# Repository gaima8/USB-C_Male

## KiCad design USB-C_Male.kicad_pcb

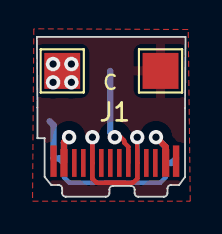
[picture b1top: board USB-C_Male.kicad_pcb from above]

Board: 2 copper layers, 8.3 x 8.9 mm, 4 parts (1 on the bottom side), 3 nets.

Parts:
J1: USB_C_Receptacle_PowerOnly_6P; USB_C_Plug_JAE_DX07P024AJ1
J2: V; TestPoint_Pad_2.0x2.0mm
J3: C; TestPoint_Pad_2.0x2.0mm
J4: G; TestPoint_Pad_2.0x2.0mm

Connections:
CC: J1.A5 (CC), J3.1
GND: J1.A1 (GND), J1.A12 (GND), J1.B1 (GND), J1.B12 (GND), J1.S1 (SHIELD), J4.1
VBUS: J1.A4 (VBUS), J1.A9 (VBUS), J1.B4 (VBUS), J1.B9 (VBUS), J2.1

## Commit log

2023-11-05 initial
2023-11-05 nets and fills
